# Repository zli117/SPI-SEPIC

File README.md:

# SPI-SEPIC
SPI controlled SEPIC boost buck converter.

Input voltage range: 5\~24V
Output voltage range: 2.5\~24V

## Schematic

## PCB

Front                         |  Back
:----------------------------:|:----------------------------:
  |  
     |  

## Parts

Ref # | Name | Link
:---:|:-----:|:----:
R1 | 220 Resister | Generic Part
R2 | 15k Resister | https://www.digikey.com/en/products/detail/koa-speer-electronics-inc/CF1-4CT52R153J/13537263
R3 | 1.24k Resister | https://www.digikey.com/en/products/detail/yageo/MFR-25FBF52-1K24/13029
R4 | 2.2k Resister | https://www.digikey.com/en/products/detail/koa-speer-electronics-inc/CF1-4CT52R222J/13537295
U1 | AP2205-33Y-13 | https://www.digikey.com/en/products/detail/diodes-incorporated/AP2205-33Y-13/10107162
U2 | XL6009 | https://www.haoyuelectronics.com/Attachment/XL6009/XL6009-DC-DC-Converter-Datasheet.pdf
U3 | MCP48FVB21-E/UN | https://www.digikey.com/en/products/detail/microchip-technology/MCP48FVB21-E-UN/5773466
D1 | SB5H100-E3/73 | https://www.digikey.com/en/products/detail/vishay-general-semiconductor-diodes-division/SB5H100-E3-73/9600329?s=N4IgTCBcDaIMoCECsAJAjABgwWgKIGYB6AdnxAF0BfIA
D2 | 5mm LED | Generic Part
C1 | UVR1H471MHD1TO | https://www.digikey.com/en/products/detail/nichicon/UVR1H471MHD1TO/4328413
C2 | CGA3E1X7R1V105M080AC | https://www.digikey.com/en/products/detail/tdk-corporation/CGA3E1X7R1V105M080AC/4931462
C3 | 100ZLJ220M12.5X25 | https://www.digikey.com/en/products/detail/rubycon/100ZLJ220M12-5X25/3133967
C4 | C1005X6S0G225K050BC | https://www.digikey.com/en/products/detail/tdk-corporation/C1005X6S0G225K050BC/3951112
C5 | EEU-FC1J471 | https://www.digikey.com/en/products/detail/panasonic-electronic-components/EEU-FC1J471/266361
C6 C7 C8 C9 | 04025C102KAT2A | https://www.digikey.com/en/products/detail/kyocera-avx/04025C102KAT2A/563211
L1 and L2 | 1410454C | https://www.digikey.com/en/products/detail/murata-power-solutions-inc/1410454C/1924845

## SPI Command

See [MCP48FVBXX doc](https://ww1.microchip.com/downloads/en/DeviceDoc/20005466A.pdf) for the full details. For simple writes, send the following 24-bit command: 

Let `val` be the value of the 12-bit DAC. Value in range `[0, 4096)`)

Byte 0 | Byte 1 | Byte 2
:---:|:-----:|:----:
All 0 | `val >> 8` | `val & 0xFF`

Note that due to part tolerances, you might need to calibrate the mapping with max output voltage (`val = 4095`) and min output voltage (`val = 0`)

## Change Log

 * v0.1: Initial version

This work is licensed under a
[Creative Commons Attribution-ShareAlike 4.0 International License][cc-by-sa].

[![CC BY-SA 4.0][cc-by-sa-image]][cc-by-sa]

[cc-by-sa]: http://creativecommons.org/licenses/by-sa/4.0/
[cc-by-sa-image]: https://licensebuttons.net/l/by-sa/4.0/88x31.png
[cc-by-sa-shield]: https://img.shields.io/badge/License-CC%20BY--SA%204.0-lightgrey.svg

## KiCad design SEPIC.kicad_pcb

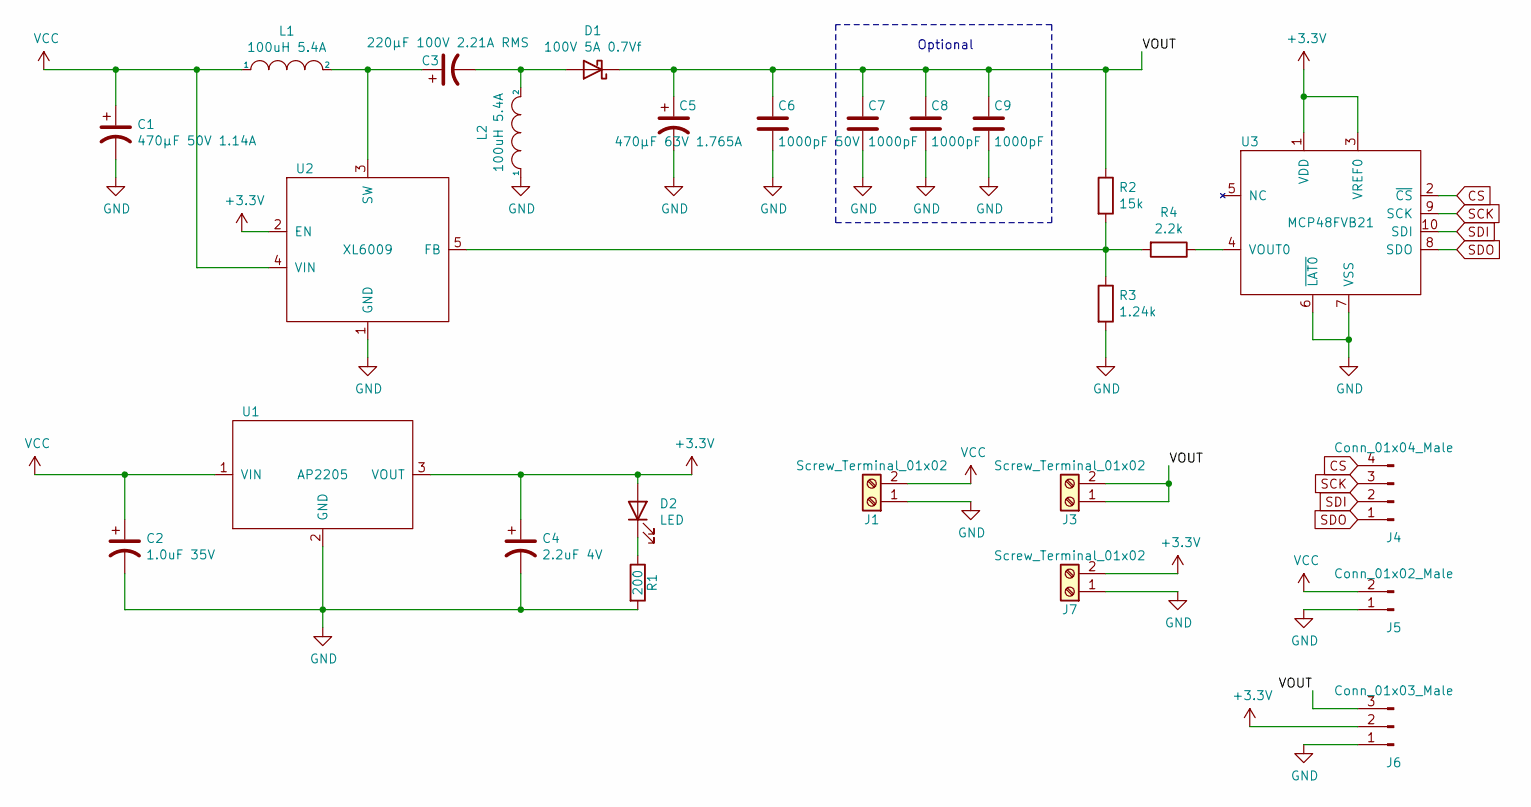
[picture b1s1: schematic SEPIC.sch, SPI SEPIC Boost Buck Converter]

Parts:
C1: 470µF 50V 1.14A; UVR1H471MHD1TO
C2: 1.0uF 35V; CGA3E1X7R1V105M080AC
C3: 220µF 100V 2.21A RMS; 100ZLJ220M12.5X25
C4: 2.2uF 4V; C1005X6S0G225K050BC
C5: 470µF 63V 1.765A; EEU-FC1J471
C6: 1000pF 50V; 04025C102KAT2A
C7, C8, C9: 1000pF; 04025C102KAT2A
D1: 100V 5A 0.7Vf; SB5H100-E3
D2: LED; LED_D5.0mm
J1, J3, J7: Screw_Terminal_01x02; 691137710002
J4: Conn_01x04_Male; PinHeader_1x04_P2.54mm_Vertical
J5: Conn_01x02_Male; PinHeader_1x02_P2.54mm_Vertical
J6: Conn_01x03_Male; PinHeader_1x03_P2.54mm_Vertical
L1, L2: 100uH 5.4A; 1410454C
R1: 200; R_Axial_DIN0207_L6.3mm_D2.5mm_P7.62mm_Horizontal
R2: 15k; CF1_4CT52R153J
R3: 1.24k; MFR-25FBF52-1K24
R4: 2.2k; CF1_4CT52R222J
U1: AP2205; AP2205-33Y-13
U2: XL6009
U3: MCP48FVB21; MCP48FVB21-E

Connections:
+3V3: C4.1, D2.2 (A), J6.2, J7.2, U1.3 (VOUT), U2.2 (EN), U3.1 (VDD), U3.3 (VREF0)
/VOUT: C5.1, C6.1, C7.1, C8.1, C9.1, D1.1 (K), J3.1, J3.2, J6.3, R2.1
CS: J4.4, U3.2 (~CS)
GND: C1.2, C2.2, C4.2, C5.2, C6.2, C7.2, C8.2, C9.2, J1.1, J5.1, J6.1, J7.1, L2.1, R1.2, R3.2, U1.2 (GND), U2.1 (GND), U3.6 (~LAT0), U3.7 (VSS)
unnamed: C3.1, L1.2, U2.3 (SW)
unnamed: C3.2, D1.2 (A), L2.2
unnamed: D2.1 (K), R1.1
unnamed: R2.2, R3.1, R4.2, U2.5 (FB)
unnamed: R4.1, U3.4 (VOUT0)
SCK: J4.3, U3.9 (SCK)
SDI: J4.2, U3.10 (SDI)
SDO: J4.1, U3.8 (SDO)
VCC: C1.1, C2.1, J1.2, J5.2, L1.1, U1.1 (VIN), U2.4 (VIN)

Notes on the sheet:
Optional

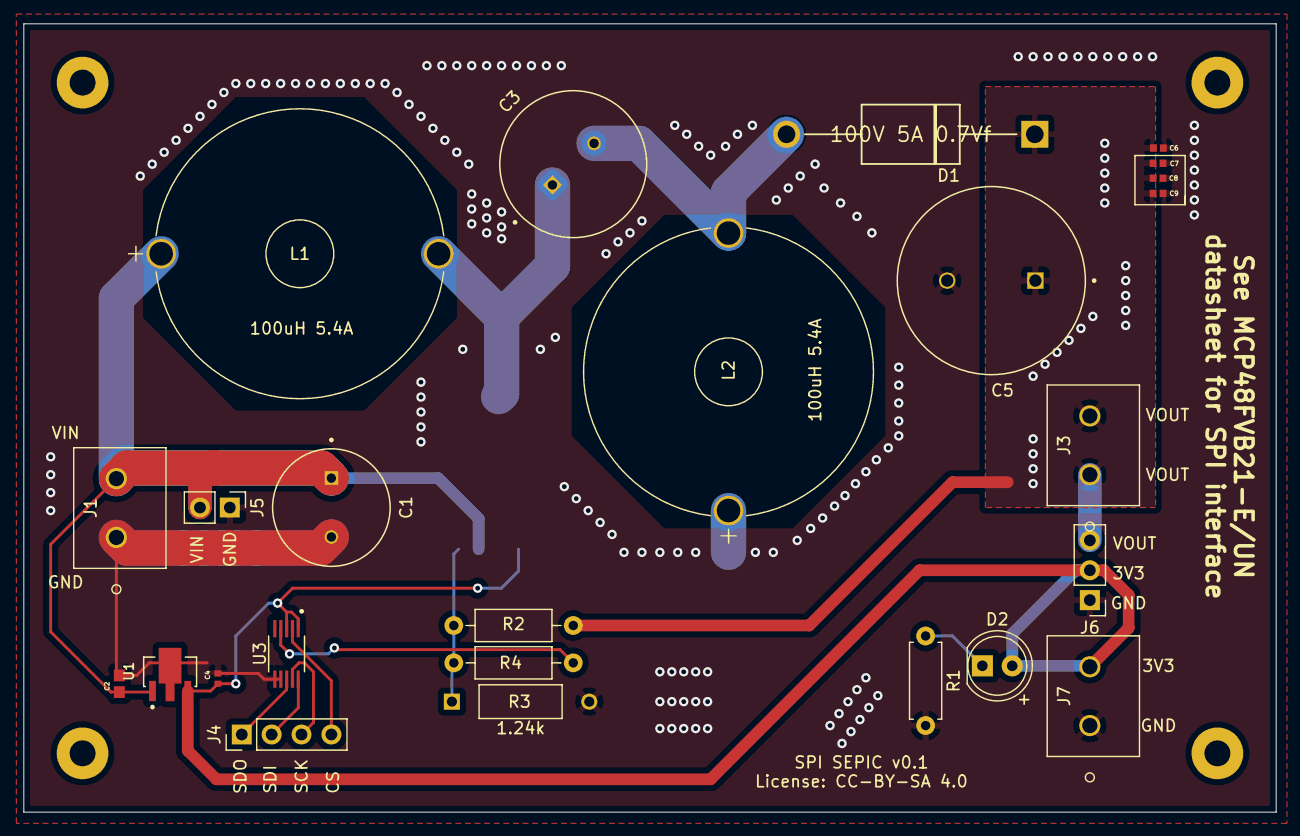
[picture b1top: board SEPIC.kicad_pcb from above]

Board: 2 copper layers, 106.5 x 67.1 mm, 26 parts (1 on the bottom side), 13 nets.

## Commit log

2021-12-17 Initial commit. PCB Basic layout
2021-12-17 Rotated C5
2021-12-17 Added cut line
2021-12-17 Mostly done
2021-12-17 Added some optional capacitors
2021-12-18 Added mounting hole
2021-12-19 Create LICENSE
2021-12-19 Updated gerber
2021-12-24 Added license related text
2021-12-24 Added images

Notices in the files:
SEPIC.kicad_pcb:
CC BY 4.0
License: CC-BY-SA 4.0
SEPIC.sch:
License CC-BY-SA 4.0 https://creativecommons.org/licenses/by-sa/4.0
parts and their libraries:
Copyright 2021 Accelerated Designs. All rights reserved.
